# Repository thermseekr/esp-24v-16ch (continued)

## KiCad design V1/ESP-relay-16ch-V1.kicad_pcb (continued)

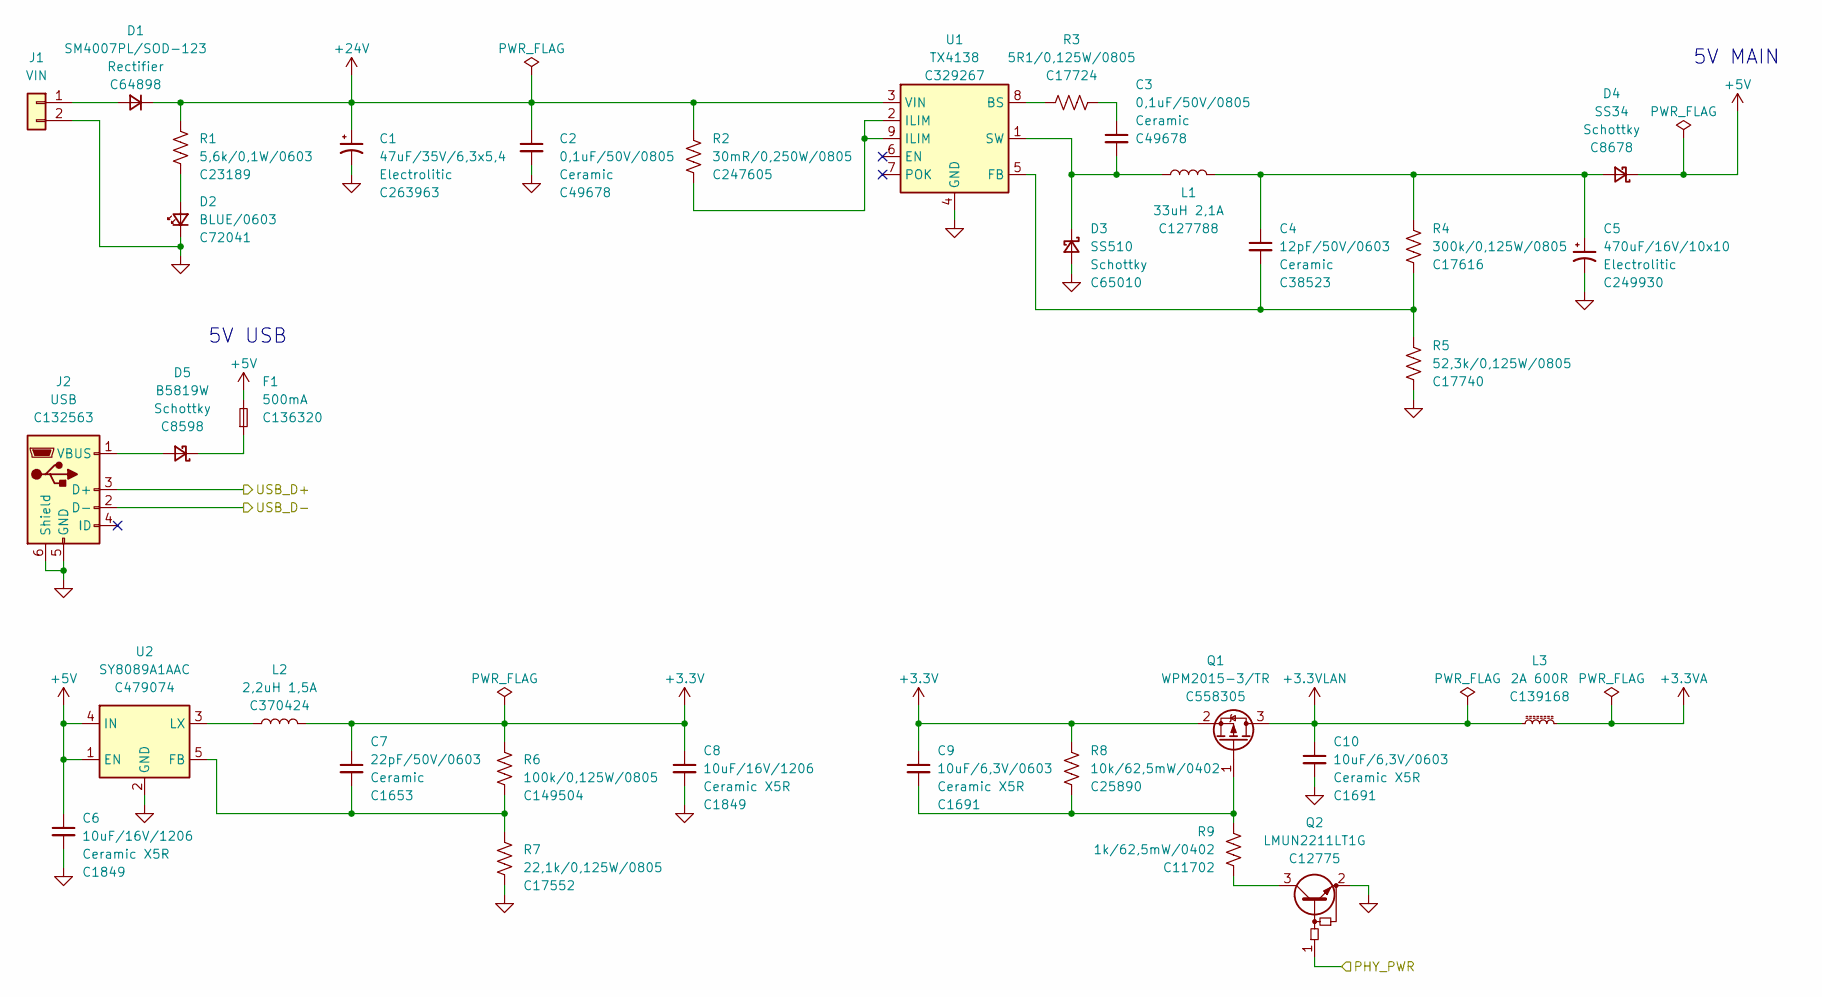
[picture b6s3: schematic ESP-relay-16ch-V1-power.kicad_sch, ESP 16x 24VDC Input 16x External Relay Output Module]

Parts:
C1: 47uF/35V/6,3x5,4; CP_Elec_6.3x5.4; Mfr PN CK1V470MCRE54; JLCPCB BOM 1
C2, C3: 0,1uF/50V/0805; C_0805_2012Metric; Mfr PN CC0805KRX7R9BB104; LCSC Part # C49678
C4: 12pF/50V/0603; C_0603_1608Metric; Mfr PN CL10C120JB8NNNC; JLCPCB BOM 1
C5: 470uF/16V/10x10; CP_Elec_10x10; Mfr PN VZH471M1CTR-1010; JLCPCB BOM 1
C6, C8: 10uF/16V/1206; C_1206_3216Metric; Mfr PN CL31A106KOHNNNE; JLCPCB BOM 1
C7: 22pF/50V/0603; C_0603_1608Metric; Mfr PN CL10C220JB8NNNC; JLCPCB BOM 1
C9, C10: 10uF/6,3V/0603; C_0603_1608Metric; Mfr PN CL10A106MQ8NNNC; JLCPCB BOM 1
D1: SM4007PL/SOD-123; D_SOD-123; Mfr PN SM4007PL; LCSC Part # C64898
D2: BLUE/0603; LED_0603_1608Metric; Mfr PN 19-217/BHC-ZL1M2RY/3T; LCSC Part # C72041
D3: SS510; D_SMA; Mfr PN SS510; JLCPCB BOM 1
D4: SS34; D_SMA; Mfr PN SS34; JLCPCB BOM 1
D5: B5819W; D_SOD-123; Mfr PN B5819W; JLCPCB BOM 1
F1: 500mA; Fuse_0402_1005Metric; Mfr PN JFC0402-0500FS; JLCPCB BOM 1
J1: VIN; TerminalBlock_Phoenix_PT-1,5-2-3.5-H_1x02_P3.50mm_Horizontal; Mfr PN 1x LM 5.08/02/90 3.5SN OR BX; JLCPCB BOM 0
J2: USB; USB_Micro-B_Amphenol_10118194_Horizontal; Mfr PN 10118194-0001LF; JLCPCB BOM 1
L1: 33uH 2,1A; L_12x12mm_H6mm; Mfr PN SWRH1205B-330MT; JLCPCB BOM 1
L2: 2,2uH 1,5A; L_3x3_H1.5; Mfr PN SPH3015H2R2MT; JLCPCB BOM 1
L3: 2A 600R; L_0805_2012Metric; Mfr PN CBM201209U601T; JLCPCB BOM 1
Q1: WPM2015-3/TR; SOT-23; Mfr PN WPM2015-3/TR; JLCPCB BOM 1
Q2: LMUN2211LT1G; SOT-23; Mfr PN LMUN2211LT1G; LCSC Part # C12775
R1: 5,6k/0,1W/0603; R_0603_1608Metric; Mfr PN 0603WAF5601T5E; LCSC Part # C23189
R2: 30mR/0,250W/0805; R_0805_2012Metric; Mfr PN 0805W4F300MT5E; LCSC Part # C247605
R3: 5R1/0,125W/0805; R_0805_2012Metric; Mfr PN 0805W8F510KT5E; LCSC Part # C17724
R4: 300k/0,125W/0805; R_0805_2012Metric; Mfr PN 0805W8F3003T5E; JLCPCB BOM 1
R5: 52,3k/0,125W/0805; R_0805_2012Metric; Mfr PN 0805W8F5232T5E; JLCPCB BOM 1
R6: 100k/0,125W/0805; R_0805_2012Metric; Mfr PN 0805W8F1003T5E; JLCPCB BOM 1
R7: 22,1k/0,125W/0805; R_0805_2012Metric; Mfr PN 0805W8F2212T5E; JLCPCB BOM 1
R8: 10k/62,5mW/0402; R_0402_1005Metric; Mfr PN 0402WGF1002TCE; LCSC Part # C25890
R9: 1k/62,5mW/0402; R_0402_1005Metric; Mfr PN 0402WGF1001TCE; LCSC Part # C11702
U1: TX4138; SOIC-8-1EP_3.9x4.9mm_P1.27mm_EP2.29x3mm_ThermalVias; Mfr PN TX4138; JLCPCB BOM 1
U2: SY8089A1AAC; TSOT-23-5; Mfr PN SY8089A1AAC; JLCPCB BOM 1

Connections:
+3.3V: C7.1, C8.1, C9.1, L2.2, Q1.2 (S), R6.1, R8.1; also elsewhere on the board
+3.3VA: L3.2; also elsewhere on the board
+3.3VLAN: C10.1, L3.1, Q1.3 (D); also elsewhere on the board
+5V: C6.1, D4.1 (K), F1.2, U2.1 (EN), U2.4 (IN)
+24V: C1.1, C2.1, D1.1 (K), R1.1, R2.1, U1.3 (VIN); also elsewhere on the board
/MCU/PHY_PWR: Q2.1 (B); also elsewhere on the board
/MCU/USB_D+: J2.3 (D+); also elsewhere on the board
/MCU/USB_D-: J2.2 (D-); also elsewhere on the board
unnamed: C3.1, R3.1
unnamed: C3.2, D3.1 (K), L1.1, U1.1 (SW)
unnamed: C4.1, C5.1, D4.2 (A), L1.2, R4.1
unnamed: C4.2, R4.2, R5.1, U1.5 (FB)
unnamed: C7.2, R6.2, R7.1, U2.5 (FB)
unnamed: C9.2, Q1.1 (G), R8.2, R9.2
unnamed: D1.2 (A), J1.1
unnamed: D2.2 (A), R1.2
unnamed: D5.1 (K), F1.1
unnamed: D5.2 (A), J2.1 (VBUS)
unnamed: L2.1, U2.3 (LX)
unnamed: Q2.3 (C), R9.1
unnamed: R2.2, U1.2 (ILIM), U1.9 (ILIM)
unnamed: R3.2, U1.8 (BS)

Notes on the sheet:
5V MAIN
5V USB

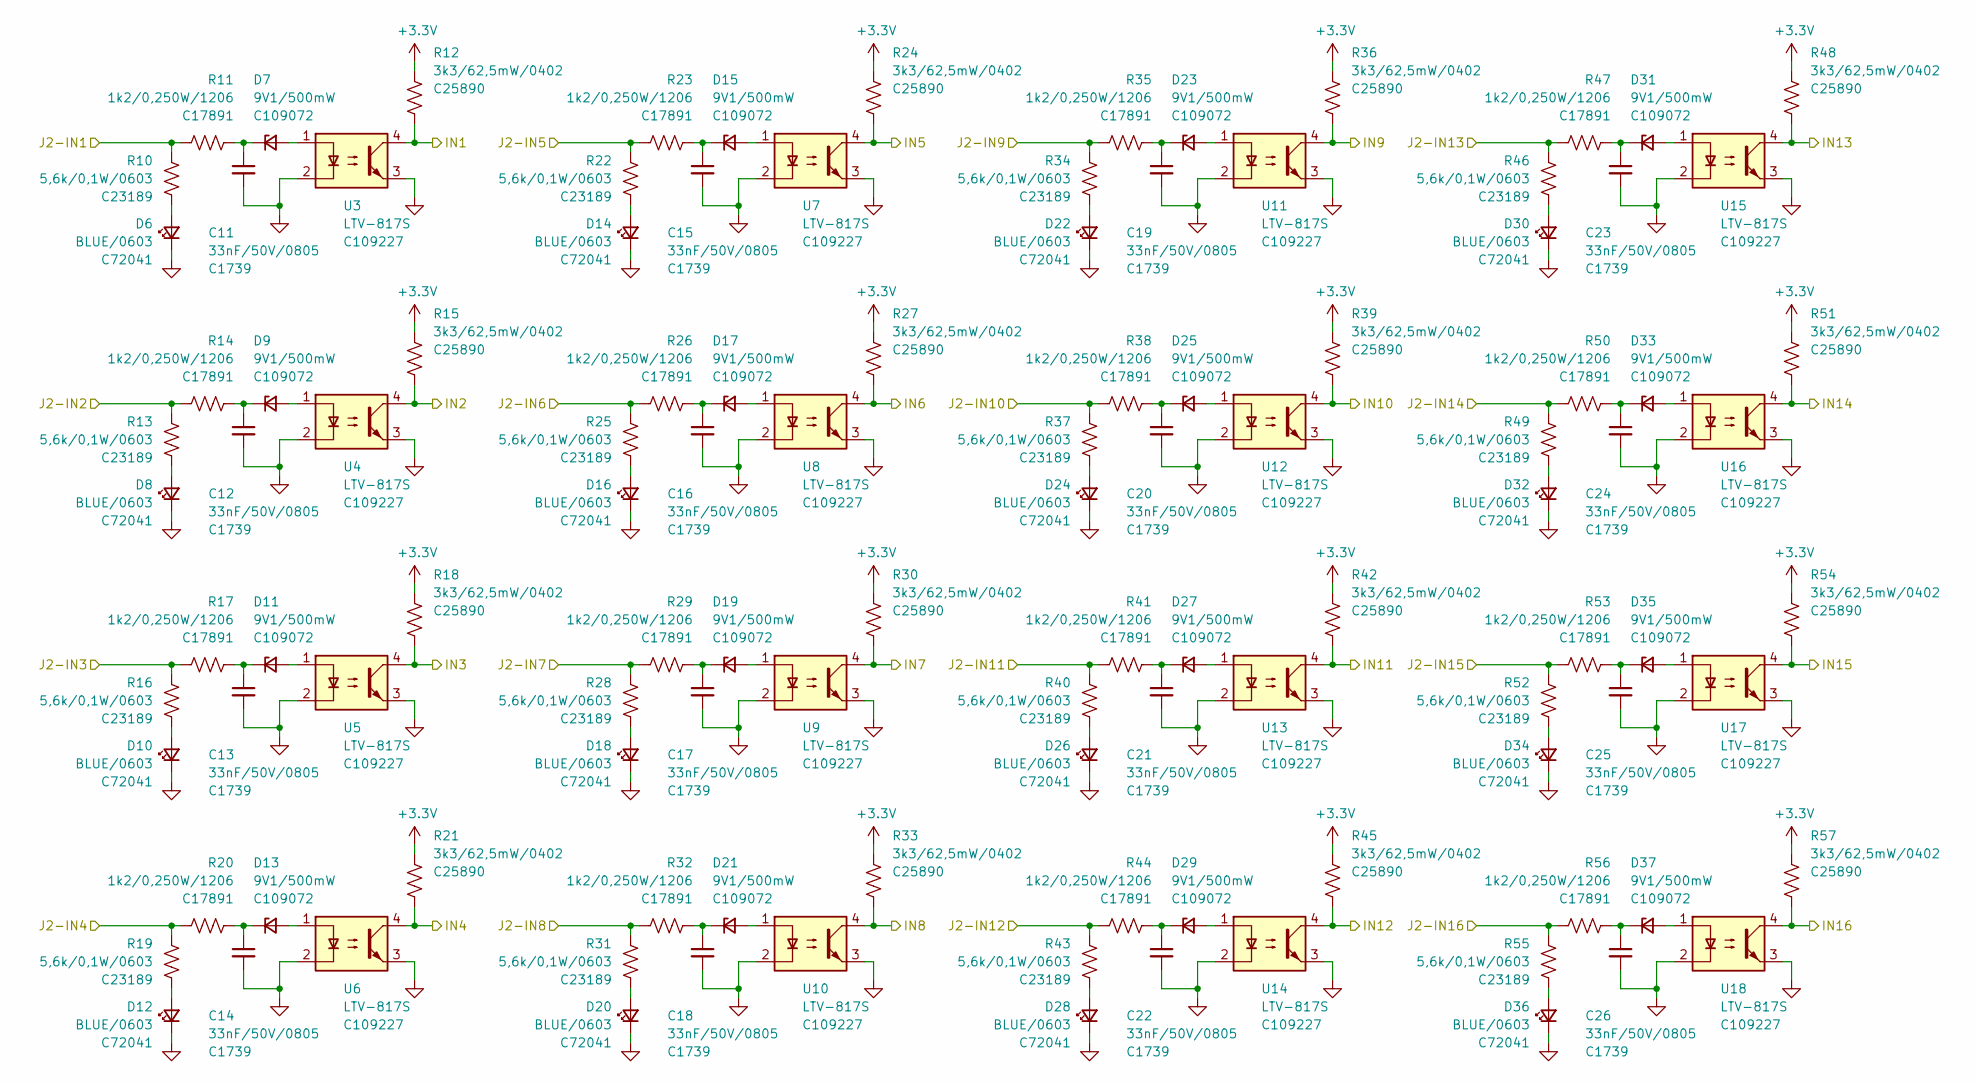
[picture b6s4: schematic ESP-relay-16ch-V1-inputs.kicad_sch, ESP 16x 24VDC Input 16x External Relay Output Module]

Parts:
C11, C12, C13, C14, C15, C16, C17, C18, C19, C20, C21, C22, C23, C24, C25, C26: 33nF/50V/0805; C_0805_2012Metric; Mfr PN 0805B333K500NT; LCSC Part # C1739
D6, D8, D10, D12, D14, D16, D18, D20, D22, D24, D26, D28, D30, D32, D34, D36: BLUE/0603; LED_0603_1608Metric; Mfr PN 19-217/BHC-ZL1M2RY/3T; LCSC Part # C72041
D7, D9, D11, D13, D15, D17, D19, D21, D23, D25, D27, D29, D31, D33, D35, D37: 9V1/500mW; D_MiniMELF; Mfr PN ZMM5239B; JLCPCB BOM 1
R10, R13, R16, R19, R22, R25, R28, R31, R34, R37, R40, R43, R46, R49, R52, R55: 5,6k/0,1W/0603; R_0603_1608Metric; Mfr PN 0603WAF5601T5E; LCSC Part # C23189
R11, R14, R17, R20, R23, R26, R29, R32, R35, R38, R41, R44, R47, R50, R53, R56: 1k2/0,250W/1206; R_1206_3216Metric; Mfr PN 1206W4F1201T5E; LCSC Part # C17891
R12, R15, R18, R21, R24, R27, R30, R33, R36, R39, R42, R45, R48, R51, R54, R57: 3k3/62,5mW/0402; R_0402_1005Metric; Mfr PN 0402WGF3301TCE; LCSC Part # C25890
U3, U4, U5, U6, U7, U8, U9, U10, U11, U12, U13, U14, U15, U16, U17, U18: LTV-817S; SMDIP-4_W9.53mm; Mfr PN LTV-817S-TA1-C; JLCPCB BOM 1

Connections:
+3.3V: R12.1, R15.1, R18.1, R21.1, R24.1, R27.1, R30.1, R33.1, R36.1, R39.1, R42.1, R45.1, R48.1, R51.1, R54.1, R57.1; also elsewhere on the board
/Inputs/IN1: R12.2, U3.4; also elsewhere on the board
/Inputs/IN2: R15.2, U4.4; also elsewhere on the board
/Inputs/IN3: R18.2, U5.4; also elsewhere on the board
/Inputs/IN4: R21.2, U6.4; also elsewhere on the board
/Inputs/IN5: R24.2, U7.4; also elsewhere on the board
/Inputs/IN6: R27.2, U8.4; also elsewhere on the board
/Inputs/IN7: R30.2, U9.4; also elsewhere on the board
/Inputs/IN8: R33.2, U10.4; also elsewhere on the board
/Inputs/IN9: R36.2, U11.4; also elsewhere on the board
/Inputs/IN10: R39.2, U12.4; also elsewhere on the board
/Inputs/IN11: R42.2, U13.4; also elsewhere on the board
/Inputs/IN12: R45.2, U14.4; also elsewhere on the board
/Inputs/IN13: R48.2, U15.4; also elsewhere on the board
/Inputs/IN14: R51.2, U16.4; also elsewhere on the board
/Inputs/IN15: R54.2, U17.4; also elsewhere on the board
/Inputs/IN16: R57.2, U18.4; also elsewhere on the board
/Inputs/J2-IN1: R10.1, R11.2; also elsewhere on the board
/Inputs/J2-IN2: R13.1, R14.2; also elsewhere on the board
/Inputs/J2-IN3: R16.1, R17.2; also elsewhere on the board
/Inputs/J2-IN4: R19.1, R20.2; also elsewhere on the board
/Inputs/J2-IN5: R22.1, R23.2; also elsewhere on the board
/Inputs/J2-IN6: R25.1, R26.2; also elsewhere on the board
/Inputs/J2-IN7: R28.1, R29.2; also elsewhere on the board
/Inputs/J2-IN8: R31.1, R32.2; also elsewhere on the board
/Inputs/J2-IN9: R34.1, R35.2; also elsewhere on the board
/Inputs/J2-IN10: R37.1, R38.2; also elsewhere on the board
/Inputs/J2-IN11: R40.1, R41.2; also elsewhere on the board
/Inputs/J2-IN12: R43.1, R44.2; also elsewhere on the board
/Inputs/J2-IN13: R46.1, R47.2; also elsewhere on the board
/Inputs/J2-IN14: R49.1, R50.2; also elsewhere on the board
/Inputs/J2-IN15: R52.1, R53.2; also elsewhere on the board
/Inputs/J2-IN16: R55.1, R56.2; also elsewhere on the board
unnamed: C11.1, D7.1 (K), R11.1
unnamed: C12.1, D9.1 (K), R14.1
unnamed: C13.1, D11.1 (K), R17.1
unnamed: C14.1, D13.1 (K), R20.1
unnamed: C15.1, D15.1 (K), R23.1
unnamed: C16.1, D17.1 (K), R26.1
unnamed: C17.1, D19.1 (K), R29.1
unnamed: C18.1, D21.1 (K), R32.1
unnamed: C19.1, D23.1 (K), R35.1
unnamed: C20.1, D25.1 (K), R38.1
unnamed: C21.1, D27.1 (K), R41.1
unnamed: C22.1, D29.1 (K), R44.1
unnamed: C23.1, D31.1 (K), R47.1
unnamed: C24.1, D33.1 (K), R50.1
unnamed: C25.1, D35.1 (K), R53.1
unnamed: C26.1, D37.1 (K), R56.1
unnamed: D6.2 (A), R10.2
unnamed: D7.2 (A), U3.1
unnamed: D8.2 (A), R13.2
unnamed: D9.2 (A), U4.1
unnamed: D10.2 (A), R16.2
unnamed: D11.2 (A), U5.1
unnamed: D12.2 (A), R19.2
unnamed: D13.2 (A), U6.1
unnamed: D14.2 (A), R22.2
unnamed: D15.2 (A), U7.1
unnamed: D16.2 (A), R25.2
unnamed: D17.2 (A), U8.1
unnamed: D18.2 (A), R28.2
unnamed: D19.2 (A), U9.1
unnamed: D20.2 (A), R31.2
unnamed: D21.2 (A), U10.1
unnamed: D22.2 (A), R34.2
unnamed: D23.2 (A), U11.1
unnamed: D24.2 (A), R37.2
unnamed: D25.2 (A), U12.1
unnamed: D26.2 (A), R40.2
unnamed: D27.2 (A), U13.1
unnamed: D28.2 (A), R43.2
unnamed: D29.2 (A), U14.1
unnamed: D30.2 (A), R46.2
unnamed: D31.2 (A), U15.1
unnamed: D32.2 (A), R49.2
unnamed: D33.2 (A), U16.1
unnamed: D34.2 (A), R52.2
unnamed: D35.2 (A), U17.1
unnamed: D36.2 (A), R55.2
unnamed: D37.2 (A), U18.1

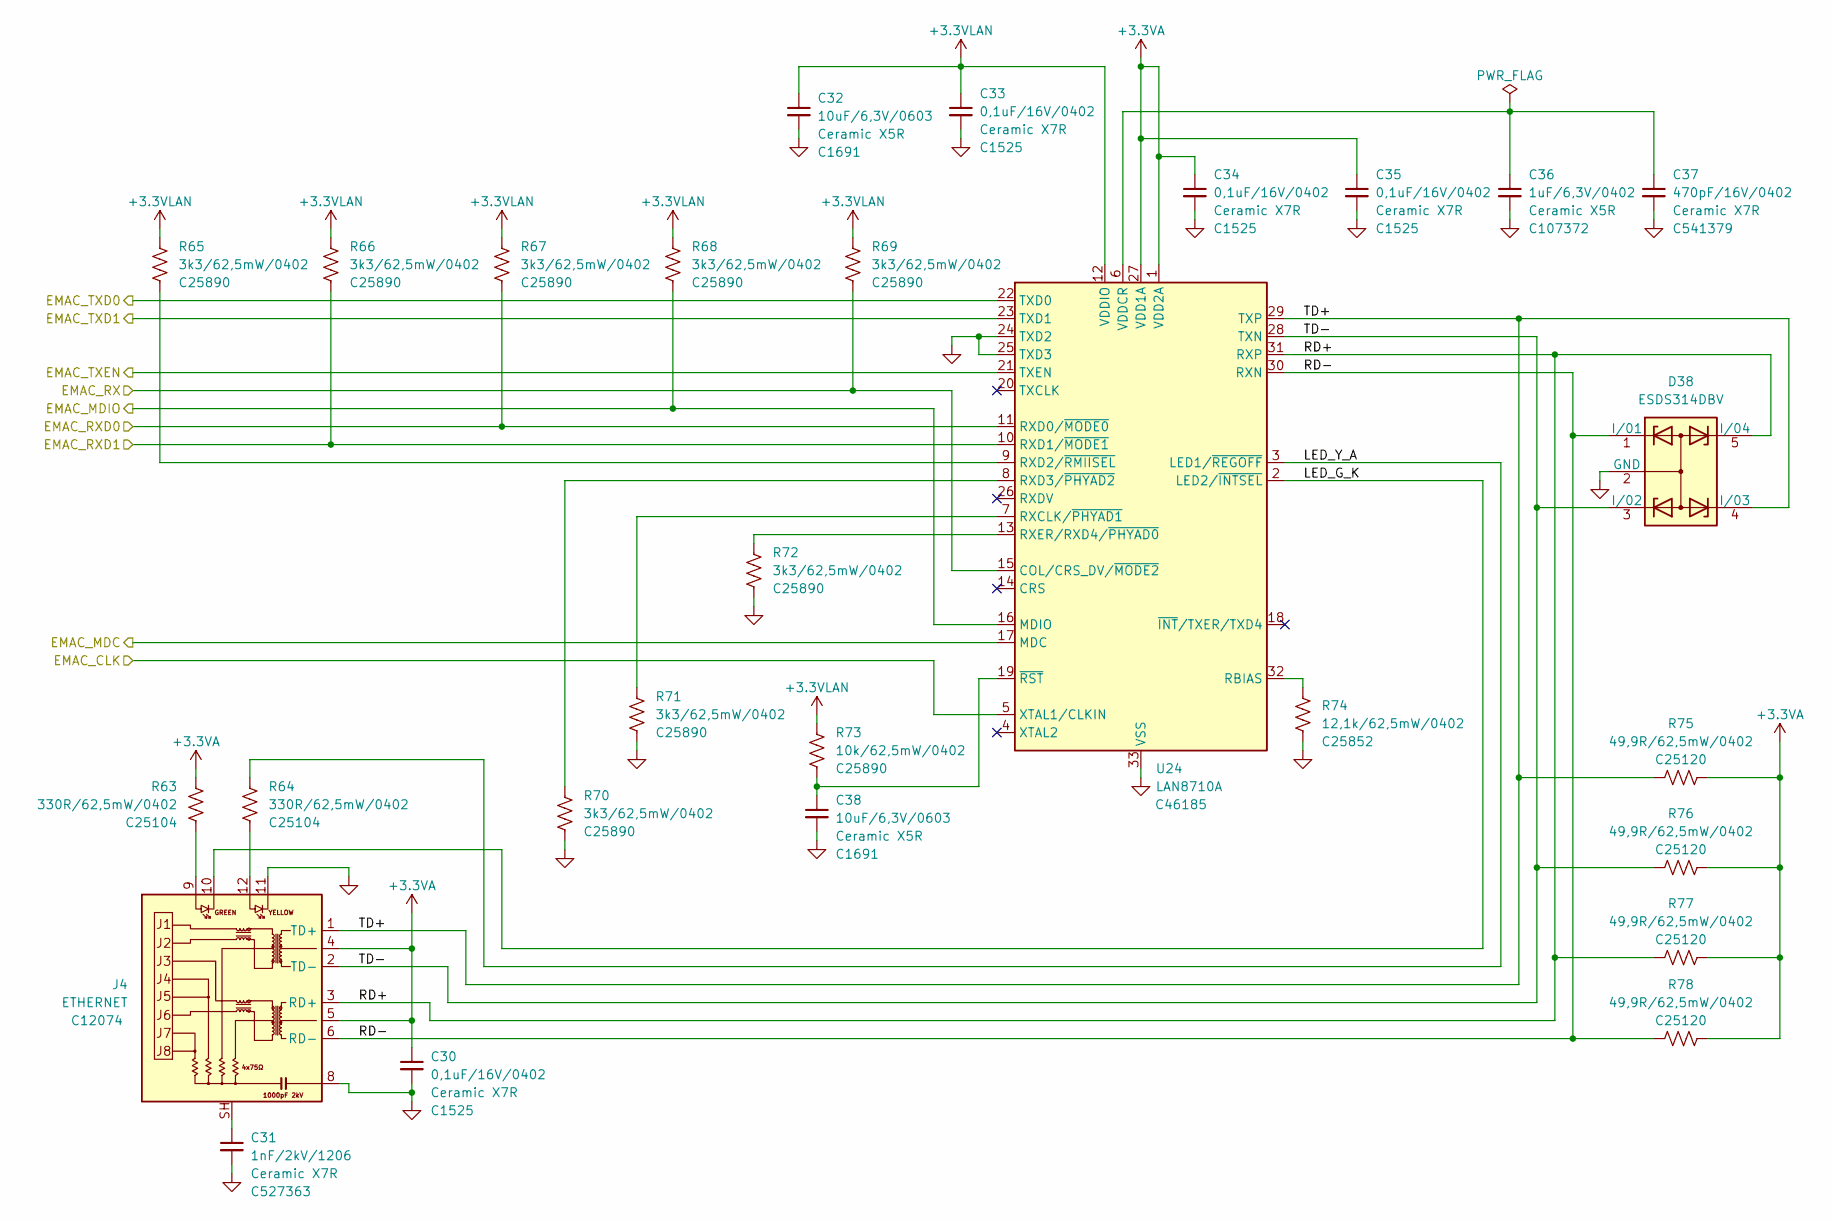
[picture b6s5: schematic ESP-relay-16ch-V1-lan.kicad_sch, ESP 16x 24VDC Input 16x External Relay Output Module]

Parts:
C30, C33, C34, C35: 0,1uF/16V/0402; C_0402_1005Metric; Mfr PN CL05B104KO5NNNC; JLCPCB BOM 1
C31: 1nF/2kV/1206; C_1206_3216Metric; Mfr PN CC1206MKX7RDBB102; JLCPCB BOM 1
C32, C38: 10uF/6,3V/0603; C_0603_1608Metric; Mfr PN CL10A106MQ8NNNC; JLCPCB BOM 1
C36: 1uF/6,3V/0402; C_0402_1005Metric; Mfr PN CL05A105KQ5NNNC; JLCPCB BOM 1
C37: 470pF/16V/0402; C_0402_1005Metric; Mfr PN CC0402KRX7R7BB471; JLCPCB BOM 1
D38: ESDS314DBV; SOT-23-5; Mfr PN ESDS314DBVR; JLCPCB BOM 1
J4: ETHERNET; RJ45_HanRun_HR911105A; Mfr PN HR911105A; JLCPCB BOM 1
R63, R64: 330R/62,5mW/0402; R_0402_1005Metric; Mfr PN 0402WGF3300TCE; LCSC Part # C25104
R65, R66, R67, R68, R69, R70, R71, R72: 3k3/62,5mW/0402; R_0402_1005Metric; Mfr PN 0402WGF3301TCE; LCSC Part # C25890
R73: 10k/62,5mW/0402; R_0402_1005Metric; Mfr PN 0402WGF1002TCE; LCSC Part # C25890
R74: 12,1k/62,5mW/0402; R_0402_1005Metric; Mfr PN 0402WGF1212TCE; JLCPCB BOM 1
R75, R76, R77, R78: 49,9R/62,5mW/0402; R_0402_1005Metric; Mfr PN 0402WGF499JTCE; LCSC Part # C25120
U24: LAN8710A; QFN-32-1EP_5x5mm_P0.5mm_EP3.3x3.3mm_ThermalVias; Mfr PN LAN8710A-EZC-TR; JLCPCB BOM 1

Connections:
+3.3VA: C30.1, C34.1, C35.1, J4.4, J4.5, R63.1, R75.2, R76.2, R77.2, R78.2, U24.1 (VDD2A), U24.27 (VDD1A); also elsewhere on the board
+3.3VLAN: C32.1, C33.1, R65.1, R66.1, R67.1, R68.1, R69.1, R73.1, U24.12 (VDDIO); also elsewhere on the board
/LAN/EMAC_CLK: U24.5 (XTAL1/CLKIN); also elsewhere on the board
/LAN/EMAC_MDC: U24.17 (MDC); also elsewhere on the board
/LAN/EMAC_MDIO: R68.2, U24.16 (MDIO); also elsewhere on the board
/LAN/EMAC_RX: R69.2, U24.15 (COL/CRS_DV/~MODE2); also elsewhere on the board
/LAN/EMAC_RXD0: R67.2, U24.11 (RXD0/~MODE0); also elsewhere on the board
/LAN/EMAC_RXD1: R66.2, U24.10 (RXD1/~MODE1); also elsewhere on the board
/LAN/EMAC_TXD0: U24.22 (TXD0); also elsewhere on the board
/LAN/EMAC_TXD1: U24.23 (TXD1); also elsewhere on the board
/LAN/EMAC_TXEN: U24.21 (TXEN); also elsewhere on the board
/LAN/LED_G_K: J4.10, U24.2 (LED2/~INTSEL)
/LAN/LED_Y_A: R64.1, U24.3 (LED1/~REGOFF)
/LAN/RD+: D38.5 (I/04), J4.3 (RD+), R77.1, U24.31 (RXP)
/LAN/RD-: D38.1 (I/01), J4.6 (RD-), R78.1, U24.30 (RXN)
/LAN/TD+: D38.4 (I/03), J4.1 (TD+), R75.1, U24.29 (TXP)
/LAN/TD-: D38.3 (I/02), J4.2 (TD-), R76.1, U24.28 (TXN)
unnamed: C31.1, J4.SH
unnamed: C36.1, C37.1, U24.6 (VDDCR)
unnamed: C38.1, R73.2, U24.19 (~RST)
unnamed: J4.9, R63.2
unnamed: J4.12, R64.2
unnamed: R65.2, U24.9 (RXD2/~RMIISEL)
unnamed: R70.1, U24.8 (RXD3/~PHYAD2)
unnamed: R71.1, U24.7 (RXCLK/~PHYAD1)
unnamed: R72.1, U24.13 (RXER/RXD4/~PHYAD0)
unnamed: R74.1, U24.32 (RBIAS)

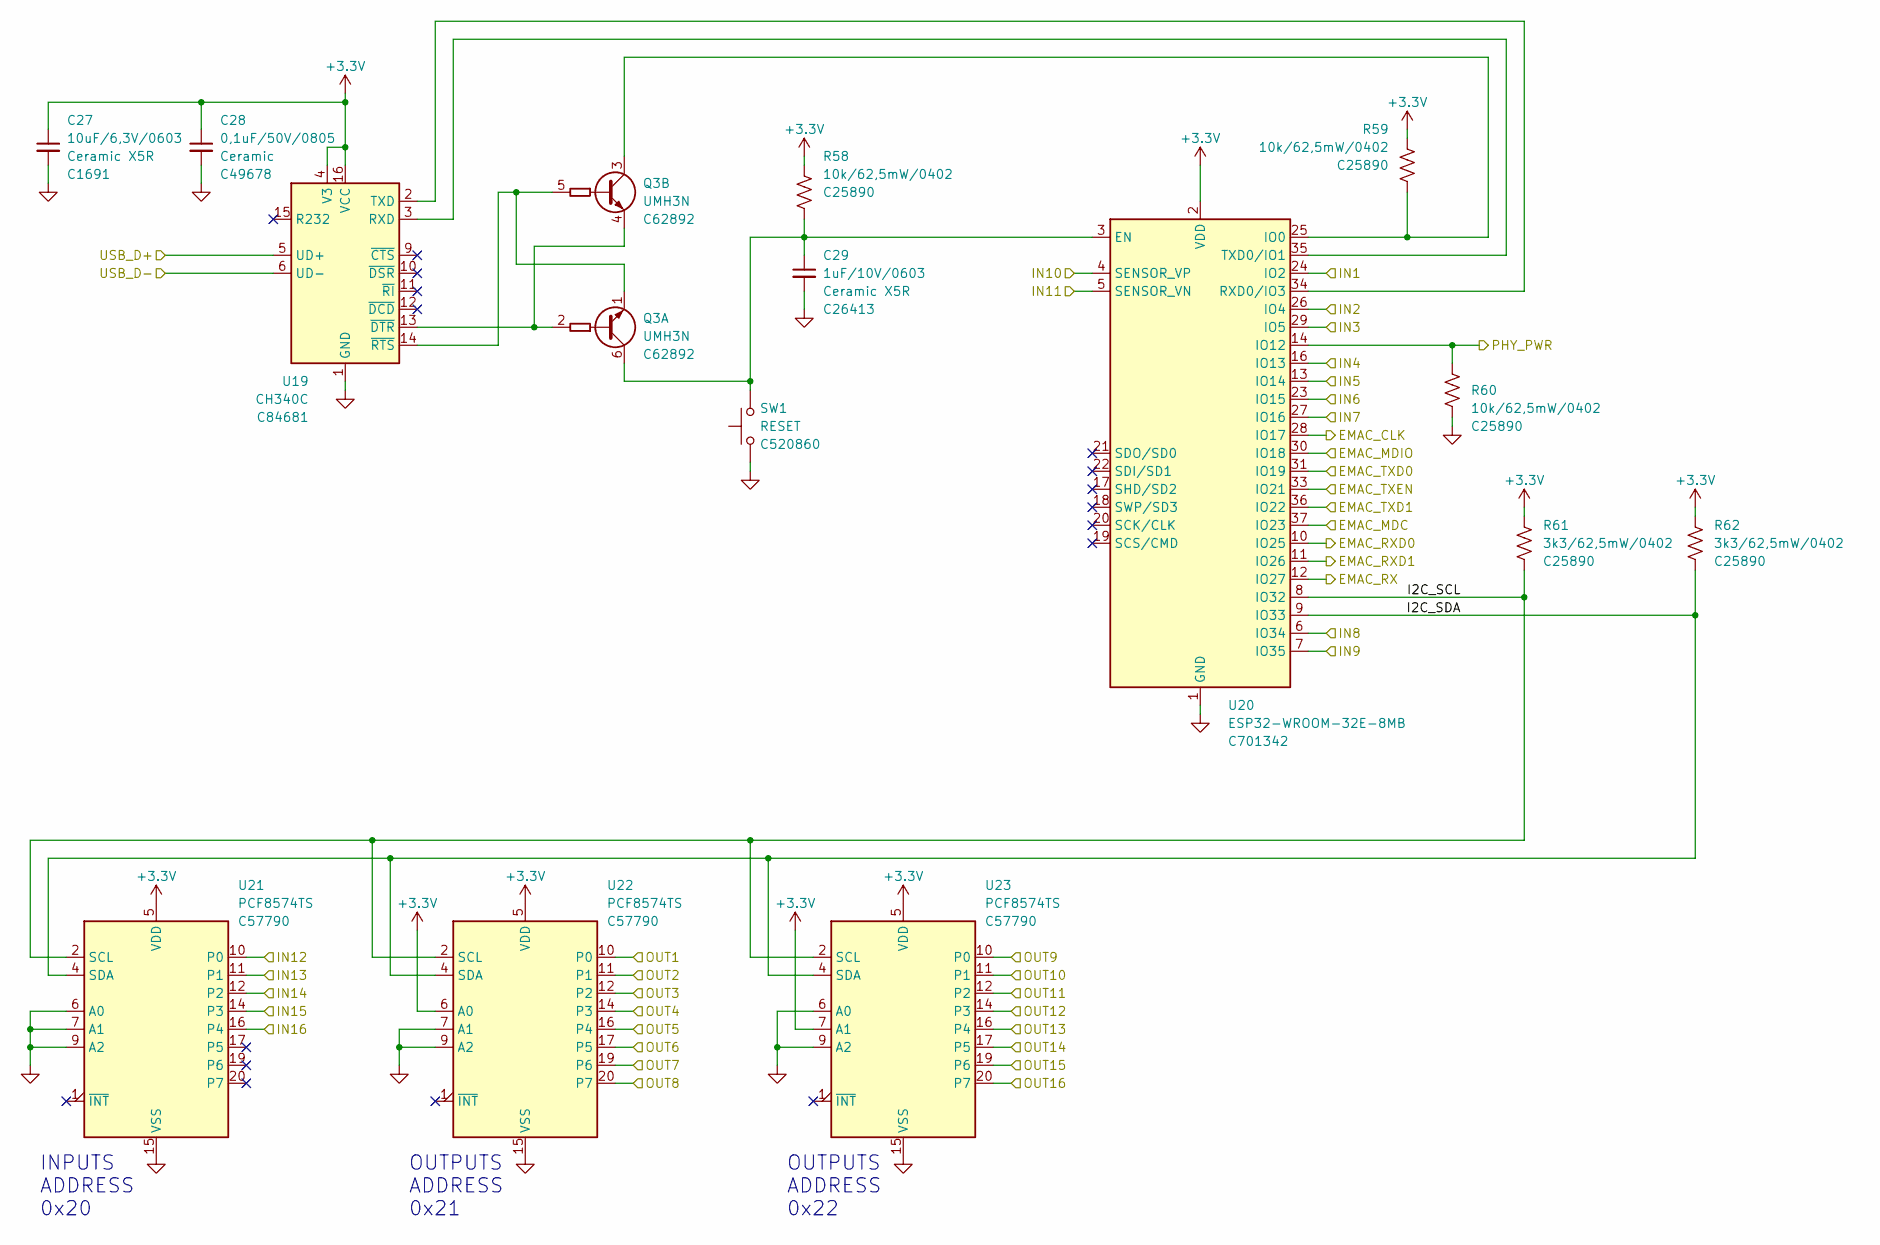
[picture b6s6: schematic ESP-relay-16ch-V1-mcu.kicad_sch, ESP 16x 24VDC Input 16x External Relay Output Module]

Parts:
C27: 10uF/6,3V/0603; C_0603_1608Metric; Mfr PN CL10A106MQ8NNNC; LCSC Part # C1691
C28: 0,1uF/50V/0805; C_0805_2012Metric; Mfr PN CC0805KRX7R9BB104; LCSC Part # C49678
C29: 1uF/10V/0603; C_0603_1608Metric; Mfr PN CL10A105KP8NNNC; JLCPCB BOM 1
Q3: UMH3N; SOT-363_SC-70-6; Mfr PN UMH3N; JLCPCB BOM 1
R58, R59, R60: 10k/62,5mW/0402; R_0402_1005Metric; Mfr PN 0402WGF1002TCE; LCSC Part # C25890
R61, R62: 3k3/62,5mW/0402; R_0402_1005Metric; Mfr PN 0402WGF3301TCE; LCSC Part # C25890
SW1: RESET; SW_SPST_Yuandi_TS1092SB3D2G; Mfr PN TS-1092S-B3D2-G; JLCPCB BOM 1
U19: CH340C; SOIC-16_3.9x9.9mm_P1.27mm; Mfr PN CH340C; JLCPCB BOM 1
U20: ESP32-WROOM-32E-8MB; ESP32-WROOM-32; Mfr PN ESP32-WROOM-32E(8MB); JLCPCB BOM 1
U21, U22, U23: PCF8574TS; SSOP-20_4.4x6.5mm_P0.65mm; Mfr PN PCF8574TS/3,118; JLCPCB BOM 1

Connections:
+3.3V: C27.1, C28.1, R58.1, R59.1, R61.1, R62.1, U19.4 (V3), U19.16 (VCC), U20.2 (VDD), U21.5 (VDD), U22.5 (VDD), U22.6 (A0), U23.5 (VDD), U23.7 (A1); also elsewhere on the board
/Inputs/IN1: U20.24 (IO2); also elsewhere on the board
/Inputs/IN2: U20.26 (IO4); also elsewhere on the board
/Inputs/IN3: U20.29 (IO5); also elsewhere on the board
/Inputs/IN4: U20.16 (IO13); also elsewhere on the board
/Inputs/IN5: U20.13 (IO14); also elsewhere on the board
/Inputs/IN6: U20.23 (IO15); also elsewhere on the board
/Inputs/IN7: U20.27 (IO16); also elsewhere on the board
/Inputs/IN8: U20.6 (IO34); also elsewhere on the board
/Inputs/IN9: U20.7 (IO35); also elsewhere on the board
/Inputs/IN10: U20.4 (SENSOR_VP); also elsewhere on the board
/Inputs/IN11: U20.5 (SENSOR_VN); also elsewhere on the board
/Inputs/IN12: U21.10 (P0); also elsewhere on the board
/Inputs/IN13: U21.11 (P1); also elsewhere on the board
/Inputs/IN14: U21.12 (P2); also elsewhere on the board
/Inputs/IN15: U21.14 (P3); also elsewhere on the board
/Inputs/IN16: U21.16 (P4); also elsewhere on the board
/LAN/EMAC_CLK: U20.28 (IO17); also elsewhere on the board
/LAN/EMAC_MDC: U20.37 (IO23); also elsewhere on the board
/LAN/EMAC_MDIO: U20.30 (IO18); also elsewhere on the board
/LAN/EMAC_RX: U20.12 (IO27); also elsewhere on the board
/LAN/EMAC_RXD0: U20.10 (IO25); also elsewhere on the board
/LAN/EMAC_RXD1: U20.11 (IO26); also elsewhere on the board
/LAN/EMAC_TXD0: U20.31 (IO19); also elsewhere on the board
/LAN/EMAC_TXD1: U20.36 (IO22); also elsewhere on the board
/LAN/EMAC_TXEN: U20.33 (IO21); also elsewhere on the board
/MCU/I2C_SCL: R61.2, U20.8 (IO32), U21.2 (SCL), U22.2 (SCL), U23.2 (SCL)
/MCU/I2C_SDA: R62.2, U20.9 (IO33), U21.4 (SDA), U22.4 (SDA), U23.4 (SDA)
/MCU/OUT1: U22.10 (P0); also elsewhere on the board
/MCU/OUT2: U22.11 (P1); also elsewhere on the board
/MCU/OUT3: U22.12 (P2); also elsewhere on the board
/MCU/OUT4: U22.14 (P3); also elsewhere on the board
/MCU/OUT5: U22.16 (P4); also elsewhere on the board
/MCU/OUT6: U22.17 (P5); also elsewhere on the board
/MCU/OUT7: U22.19 (P6); also elsewhere on the board
/MCU/OUT8: U22.20 (P7); also elsewhere on the board
/MCU/OUT9: U23.10 (P0); also elsewhere on the board
/MCU/OUT10: U23.11 (P1); also elsewhere on the board
/MCU/OUT11: U23.12 (P2); also elsewhere on the board
/MCU/OUT12: U23.14 (P3); also elsewhere on the board
/MCU/OUT13: U23.16 (P4); also elsewhere on the board
/MCU/OUT14: U23.17 (P5); also elsewhere on the board
/MCU/OUT15: U23.19 (P6); also elsewhere on the board
/MCU/OUT16: U23.20 (P7); also elsewhere on the board
/MCU/PHY_PWR: R60.1, U20.14 (IO12); also elsewhere on the board
/MCU/USB_D+: U19.5 (UD+); also elsewhere on the board
/MCU/USB_D-: U19.6 (UD-); also elsewhere on the board
unnamed: C29.1, Q3.6 (C1), R58.2, SW1.2, U20.3 (EN)
unnamed: Q3.1 (E1), Q3.5 (B2), U19.14 (~RTS)
unnamed: Q3.2 (B1), Q3.4 (E2), U19.13 (~DTR)
unnamed: Q3.3 (C2), R59.2, U20.25 (IO0)
unnamed: U19.2 (TXD), U20.34 (RXD0/IO3)
unnamed: U19.3 (RXD), U20.35 (TXD0/IO1)

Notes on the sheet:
OUTPUTS ADDRESS 0x21
OUTPUTS ADDRESS 0x22
INPUTS ADDRESS 0x20

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
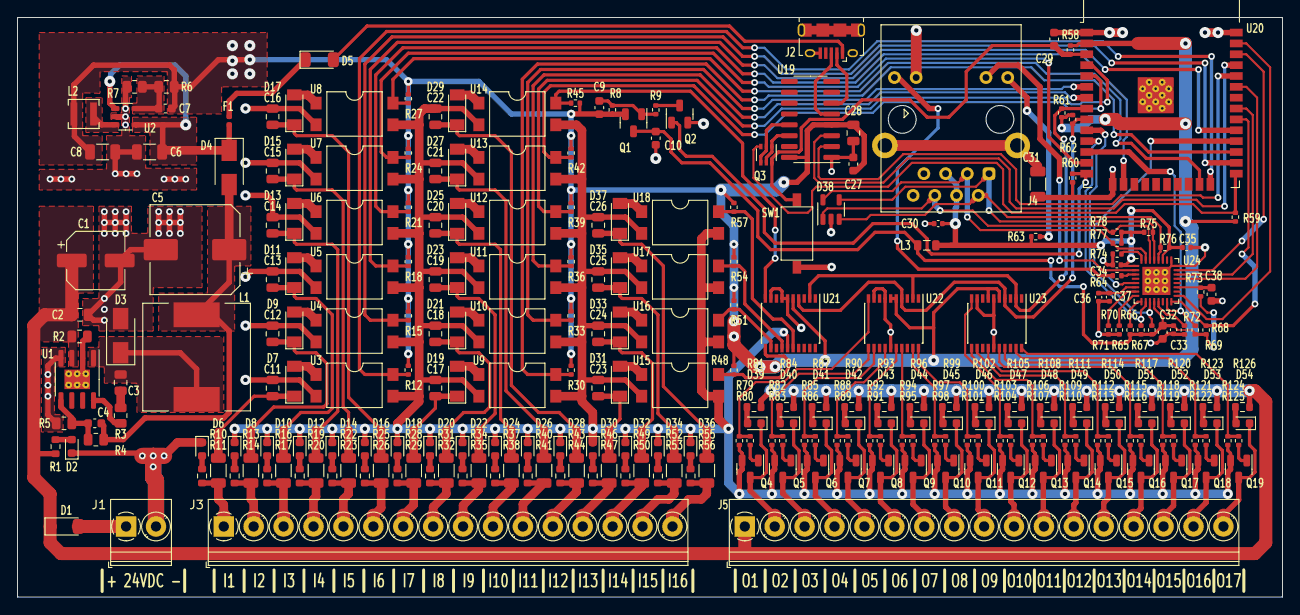
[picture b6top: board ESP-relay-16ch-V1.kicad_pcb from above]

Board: 2 copper layers, 148.0 x 67.8 mm, 271 parts (0 on the bottom side), 200 nets.

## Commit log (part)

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2022-10-17 Initial configuration
2022-10-17 Development continues
2022-10-18 Dev updates
2022-10-20 Development updates
2022-11-01 End dev start production
2023-04-20 Small adjustments to component models.
2023-04-24 Create fabrication files
2023-05-05 Project renamed
2023-05-05 Files renamed
2023-05-05 Updated references
2023-05-12 Add interrupt pins
2023-05-13 MCP interrupt signals routed
2023-05-21 Replace connector 3D models
2023-05-21 Add board image.
2023-05-21 Update silkscreen and board image.
2023-05-22 Updates for fabrication
2023-05-22 Final tweaks
2023-05-23 Adjustments for fabrication.
2023-06-23 Improvements to the PCB layout
2023-06-24 Improvements to PCB design
2023-06-24 Improvements to the PCB design
2023-06-26 Upgrade USB-Micro-B to Type-C connector.
2023-07-29 Update documentation in the schematics
2023-07-29 Added GPIO and templates info in the schematics
2023-07-30 Version 3 created
2023-07-31 Replaced R16 and R17 for a R-Pack
2023-08-19 Connectors rotated 180deg
2023-08-19 Reviewing designs
2023-08-21 Repository reorg and cleanup
2023-09-01 V3 removed
2023-09-02 Design optimization
2023-09-04 Standarization
2023-09-04 Minor updates
2023-09-04 New board image
2023-09-05 Renamed to lowercase
2023-09-06 Renaming to lowercase
2023-09-18 Adjusted footprint
2023-12-14 Documentation files
2024-06-15 Update Kicad 8
2024-10-02 Update to Kicad 8
2024-11-06 Created version 3
2024-11-06 V3 created
2024-11-18 working on v3
2024-11-22 Final touches to fabrication
2024-11-23 Final adjustments before production
2024-11-23 new file: V3/esp-24v-16ch-v3.png
2024-11-23 Upload construction files
2024-11-25 Added temperature sensor
2024-11-26 Version 3.1.0
2024-11-26 Update board image
2024-11-29 Preparations for fabrication
2025-04-09 Updating component part numbers
2025-04-14 Prefab checks
2025-04-16 Updated footprints
2025-06-23 Improvements to high speed signals routing
2025-06-27 Updated zones
2025-06-29 Added NTC inputs and redone routing
2025-06-29 Production ouput
2025-06-29 Renamed to V3.2
2025-06-29 Files for new release
2025-06-29 BOM corrected
2025-06-29 AD/DC opamp swapped for DC model
2025-06-29 Updated out of stock components
2025-06-29 Created License.txt, edited readme.md
2025-07-04 Created V4
2025-07-05 Updating PCB for V4
2025-07-05 Routing V4
2025-07-09 Added stiching vias on Tx/Rx
2025-07-13 Upgrade to Kicad 9
2025-07-13 Replaced temp/humid sensor for SHT31
2025-07-13 Final tweaks. For now.
2025-07-14 Updated to 2 NTCs instead of 4.
2025-07-14 Update fabrication files
2025-07-14 Tweaking analog routing
2025-07-14 Fabrication updates
2025-07-31 Update GPIO template info
2025-08-01 Added info about the NTC inputs
2025-08-16 Created release for V4.0
2025-08-18 Version 4.1
2025-10-04 PCB updates
2025-11-24 Adjusted version numbers
2025-11-29 Revising schematics
2025-12-01 Revising the schematics
2025-12-02 Rerouting
2025-12-09 Removed old ${REFERENCE} texts
2025-12-09 Rerouting finished
2025-12-09 Revise README for ESP-24V-16CH V5.0 changes
    Updated project description and version history for V5.0.
2025-12-09 Created V5
2025-12-10 Revising before production
2025-12-11 Preparing for fabrication
2025-12-13 Adjusted lenght of diff tracks
2026-01-06 Updates and corrections to SCH and PCB
2026-01-06 Updated version to 5.1
2026-01-06 Updated README
    Updated version history with a link to the contributor's GitHub profile.
2026-01-24 V5.2.0
2026-01-24 Back to V5.1.0
2026-02-04 Many changes!
2026-02-10 MCP23017 GPA7 and GPB7 disabled.
2026-02-10 V5.2
2026-02-10 Add version history for ESP-24V-16CH V5.2
    Updated version history for ESP-24V-16CH to include changes in V5.2, such as disabling specific pins and reassigning inputs.
2026-02-10 Revise README for improved clarity and details
    Updated README to clarify input/output specifications and added hardware specifications table.
2026-02-11 Update README for clarity on input/output types
2026-02-11 Improvements to the silkscreen
2026-02-11 Erase old files
2026-02-18 Reviewed capacitor sizes and voltages.
2026-02-21 Removed INTB connection from inputs MCP23017
2026-03-04 Inputs GND separated from main GND.
2026-03-06 Tweaks to PCB
2026-06-01 3.5mm pitch connectors
